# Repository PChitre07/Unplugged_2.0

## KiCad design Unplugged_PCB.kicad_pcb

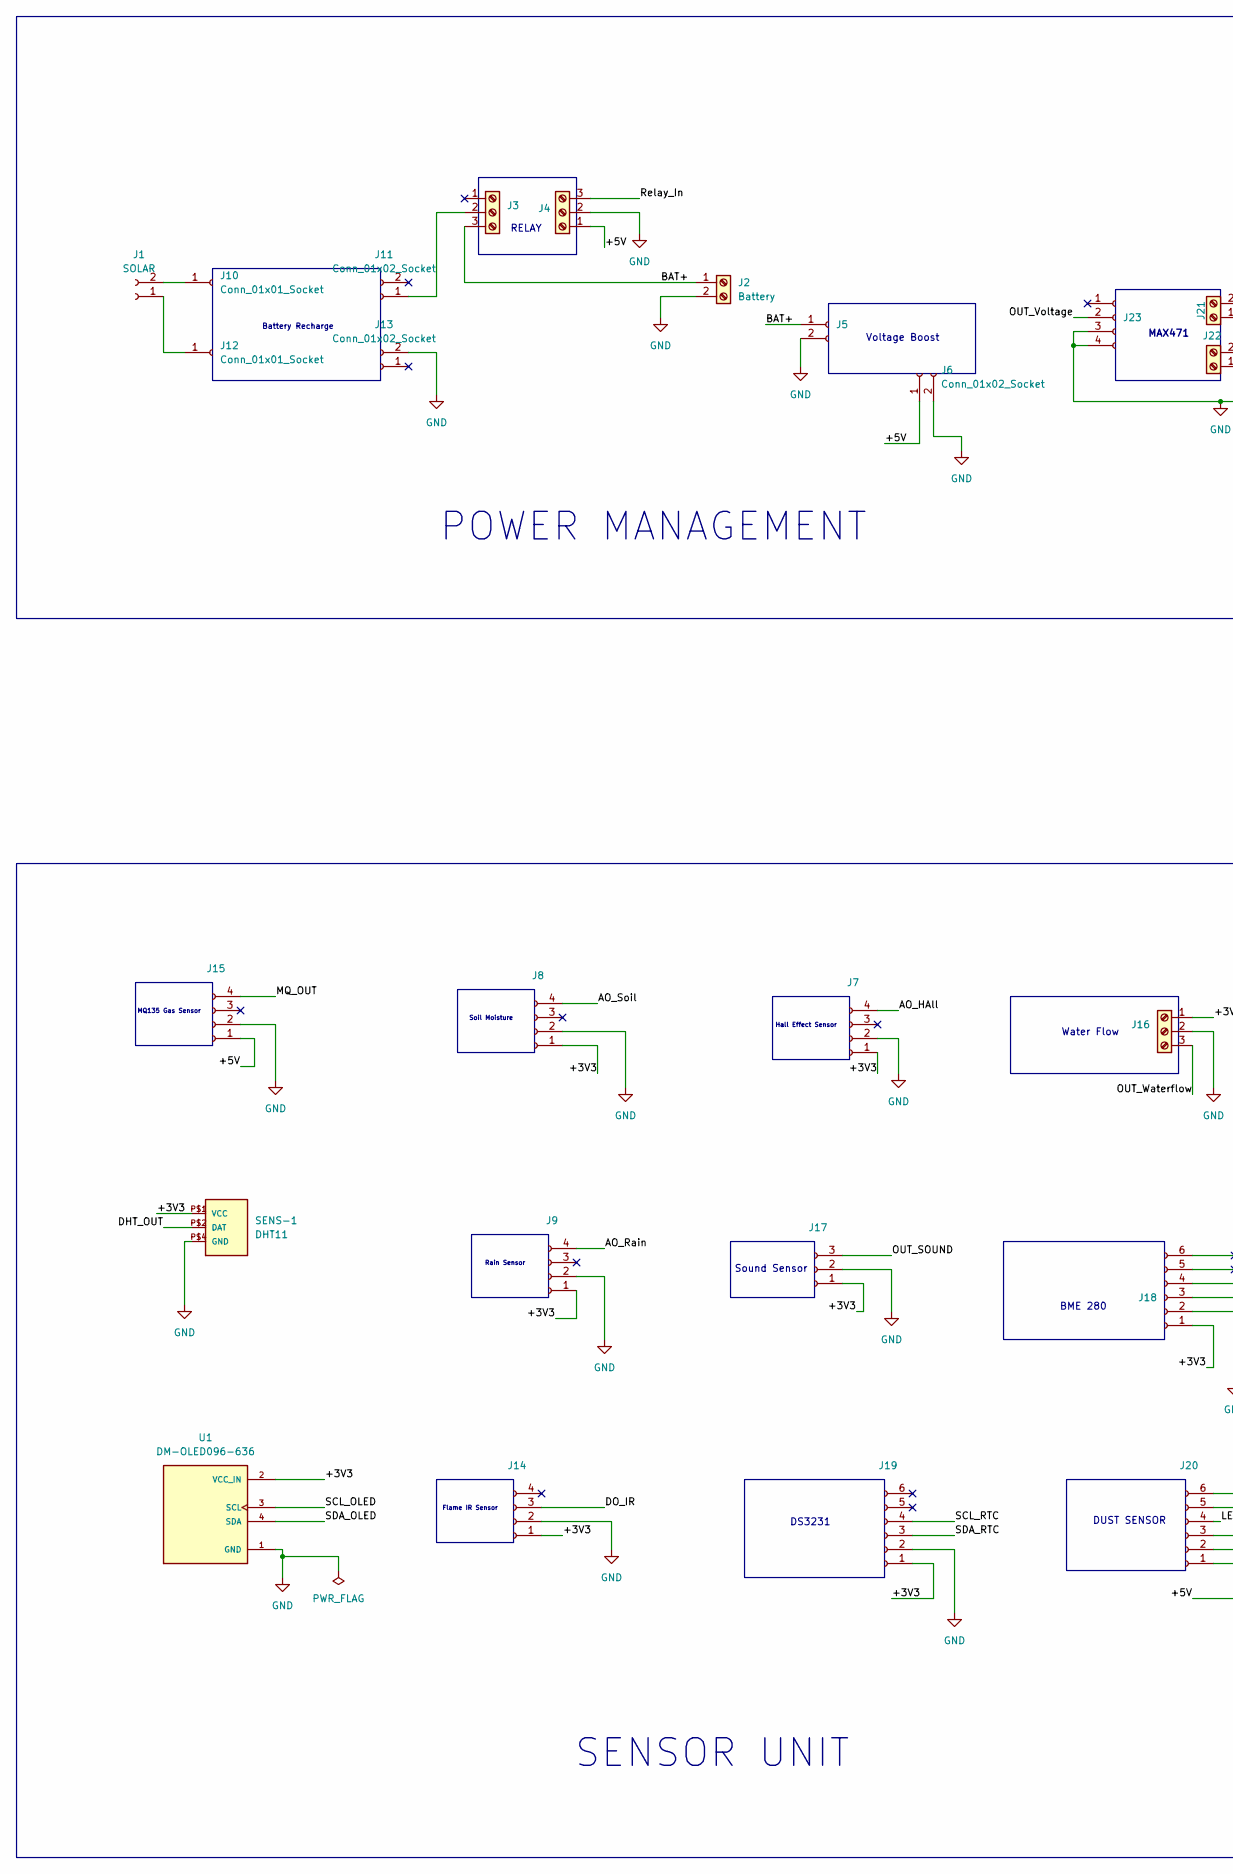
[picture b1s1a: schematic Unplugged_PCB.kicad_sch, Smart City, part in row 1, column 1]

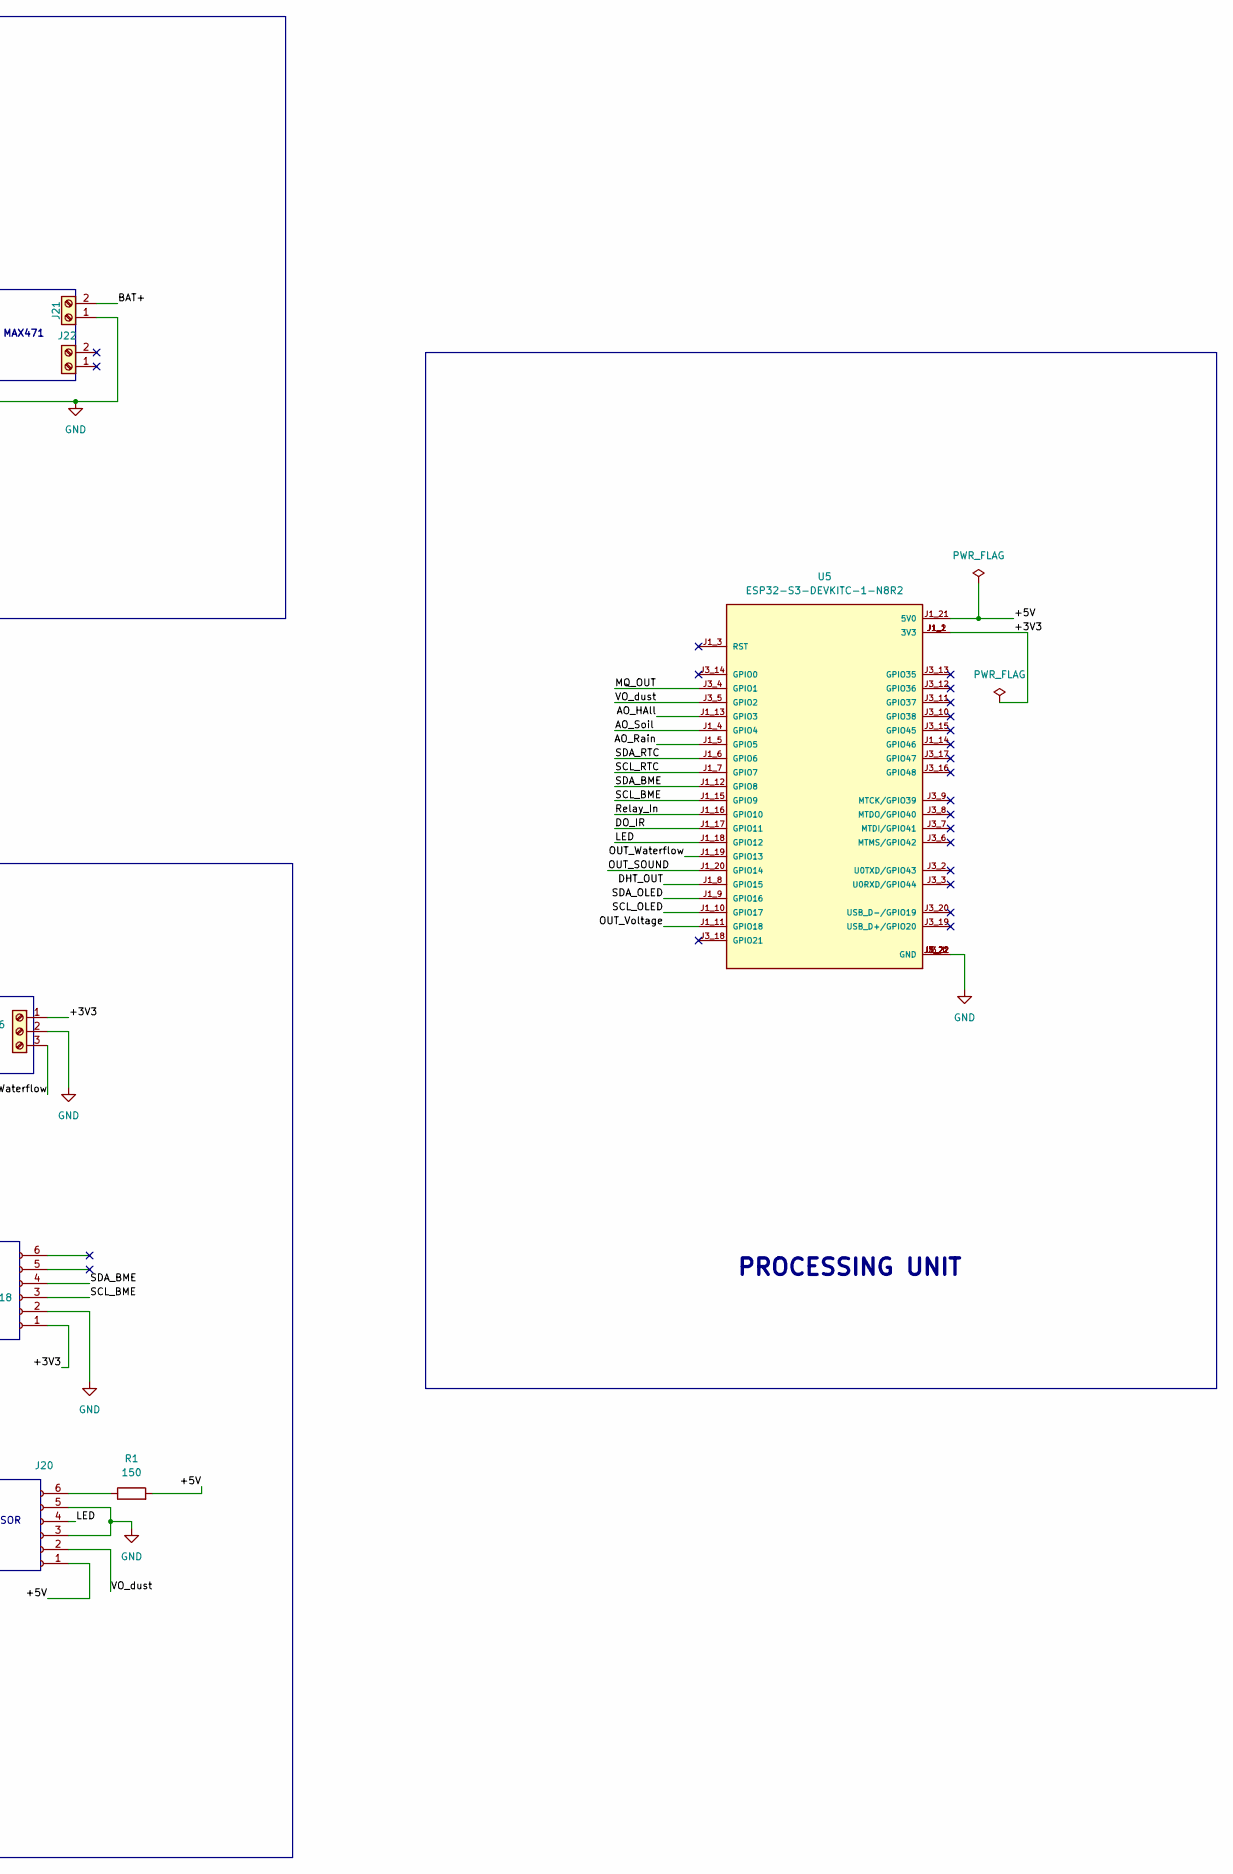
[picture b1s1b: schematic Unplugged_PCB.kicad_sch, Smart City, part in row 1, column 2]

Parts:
J1: SOLAR; PinSocket_1x02_P2.54mm_Vertical
J2: Battery; TerminalBlock_bornier-2_P5.08mm
J3, J4, J16: Screw_Terminal_01x03; TerminalBlock_bornier-3_P5.08mm
J5, J6, J11, J13: Conn_01x02_Socket; PinSocket_1x02_P2.54mm_Vertical
J7, J8, J9, J14, J15, J23: Conn_01x04_Socket; PinSocket_1x04_P2.54mm_Vertical
J10, J12: Conn_01x01_Socket; PinSocket_1x01_P2.54mm_Vertical
J17: Conn_01x03_Socket; PinSocket_1x03_P2.54mm_Vertical
J18, J19, J20: Conn_01x06_Socket; PinSocket_1x06_P2.54mm_Vertical
J21, J22: Screw_Terminal_01x02; TerminalBlock_bornier-2_P5.08mm
R1: 150; R_Axial_DIN0207_L6.3mm_D2.5mm_P7.62mm_Horizontal
SENS-1: DHT11; SENSOR-DHT11
U1: DM-OLED096-636; MODULE_DM-OLED096-636; PARTREV 2018-09-10
U5: ESP32-S3-DEVKITC-1-N8R2; XCVR_ESP32-S3-DEVKITC-1-N8R2; PARTREV V1

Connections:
/+3V3: J7.1, J8.1, J9.1, J14.1, J16.1, J17.1, J18.1, J19.1, SENS-1.P$1 (VCC), U1.2 (VCC_IN), U5.J1_1 (3V3), U5.J1_2 (3V3)
/+5V: J4.1, J6.1, J15.1, J20.1, R1.2, U5.J1_21 (5V0)
/AO_HAll: J7.4, U5.J1_13 (GPIO3)
/AO_Rain: J9.4, U5.J1_5 (GPIO5)
/AO_Soil: J8.4, U5.J1_4 (GPIO4)
/BAT+: J2.1, J3.3, J5.1, J21.2
/DHT_OUT: SENS-1.P$2 (DAT), U5.J1_8 (GPIO15)
/DO_IR: J14.3, U5.J1_17 (GPIO11)
/LED: J20.4, U5.J1_18 (GPIO12)
/MQ_OUT: J15.4, U5.J3_4 (GPIO1)
/OUT_SOUND: J17.3, U5.J1_20 (GPIO14)
/OUT_Voltage: J23.2, U5.J1_11 (GPIO18)
/OUT_Waterflow: J16.3, U5.J1_19 (GPIO13)
/Relay_In: J4.3, U5.J1_16 (GPIO10)
/SCL_BME: J18.3, U5.J1_15 (GPIO9)
/SCL_OLED: U1.3 (SCL), U5.J1_10 (GPIO17)
/SCL_RTC: J19.4, U5.J1_7 (GPIO7)
/SDA_BME: J18.4, U5.J1_12 (GPIO8)
/SDA_OLED: U1.4 (SDA), U5.J1_9 (GPIO16)
/SDA_RTC: J19.3, U5.J1_6 (GPIO6)
/VO_dust: J20.2, U5.J3_5 (GPIO2)
GND: J2.2, J4.2, J5.2, J6.2, J7.2, J8.2, J9.2, J13.2, J14.2, J15.2, J16.2, J17.2, J18.2, J19.2, J20.3, J20.5, J21.1, J23.3, J23.4, SENS-1.P$4 (GND), U1.1 (GND), U5.J1_22 (GND), U5.J3_1 (GND), U5.J3_21 (GND), U5.J3_22 (GND)
unnamed: J1.1, J12.1
unnamed: J1.2, J10.1
unnamed: J3.2, J11.1
unnamed: J20.6, R1.1

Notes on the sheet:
Water Flow
BME 280
Rain Sensor
RELAY
Hall Effect Sensor
POWER MANAGEMENT
DUST SENSOR
Battery Recharge
Flame IR Sensor
Voltage Boost
PROCESSING UNIT
MQ135 Gas Sensor
DS3231
SENSOR UNIT
MAX471
Soil Moisture
Sound Sensor

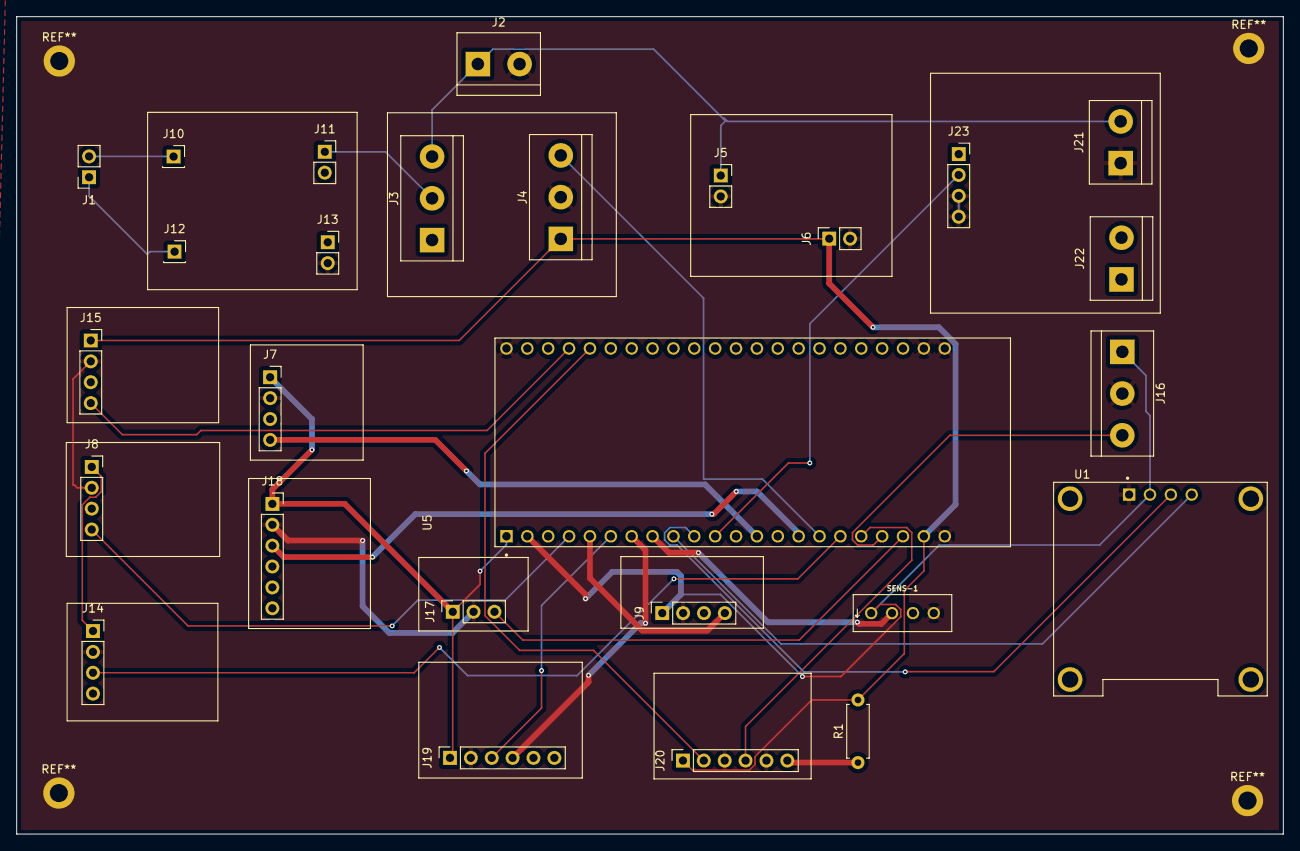
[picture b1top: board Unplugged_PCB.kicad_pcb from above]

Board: 2 copper layers, 154.2 x 99.5 mm, 27 parts (0 on the bottom side), 26 nets.
